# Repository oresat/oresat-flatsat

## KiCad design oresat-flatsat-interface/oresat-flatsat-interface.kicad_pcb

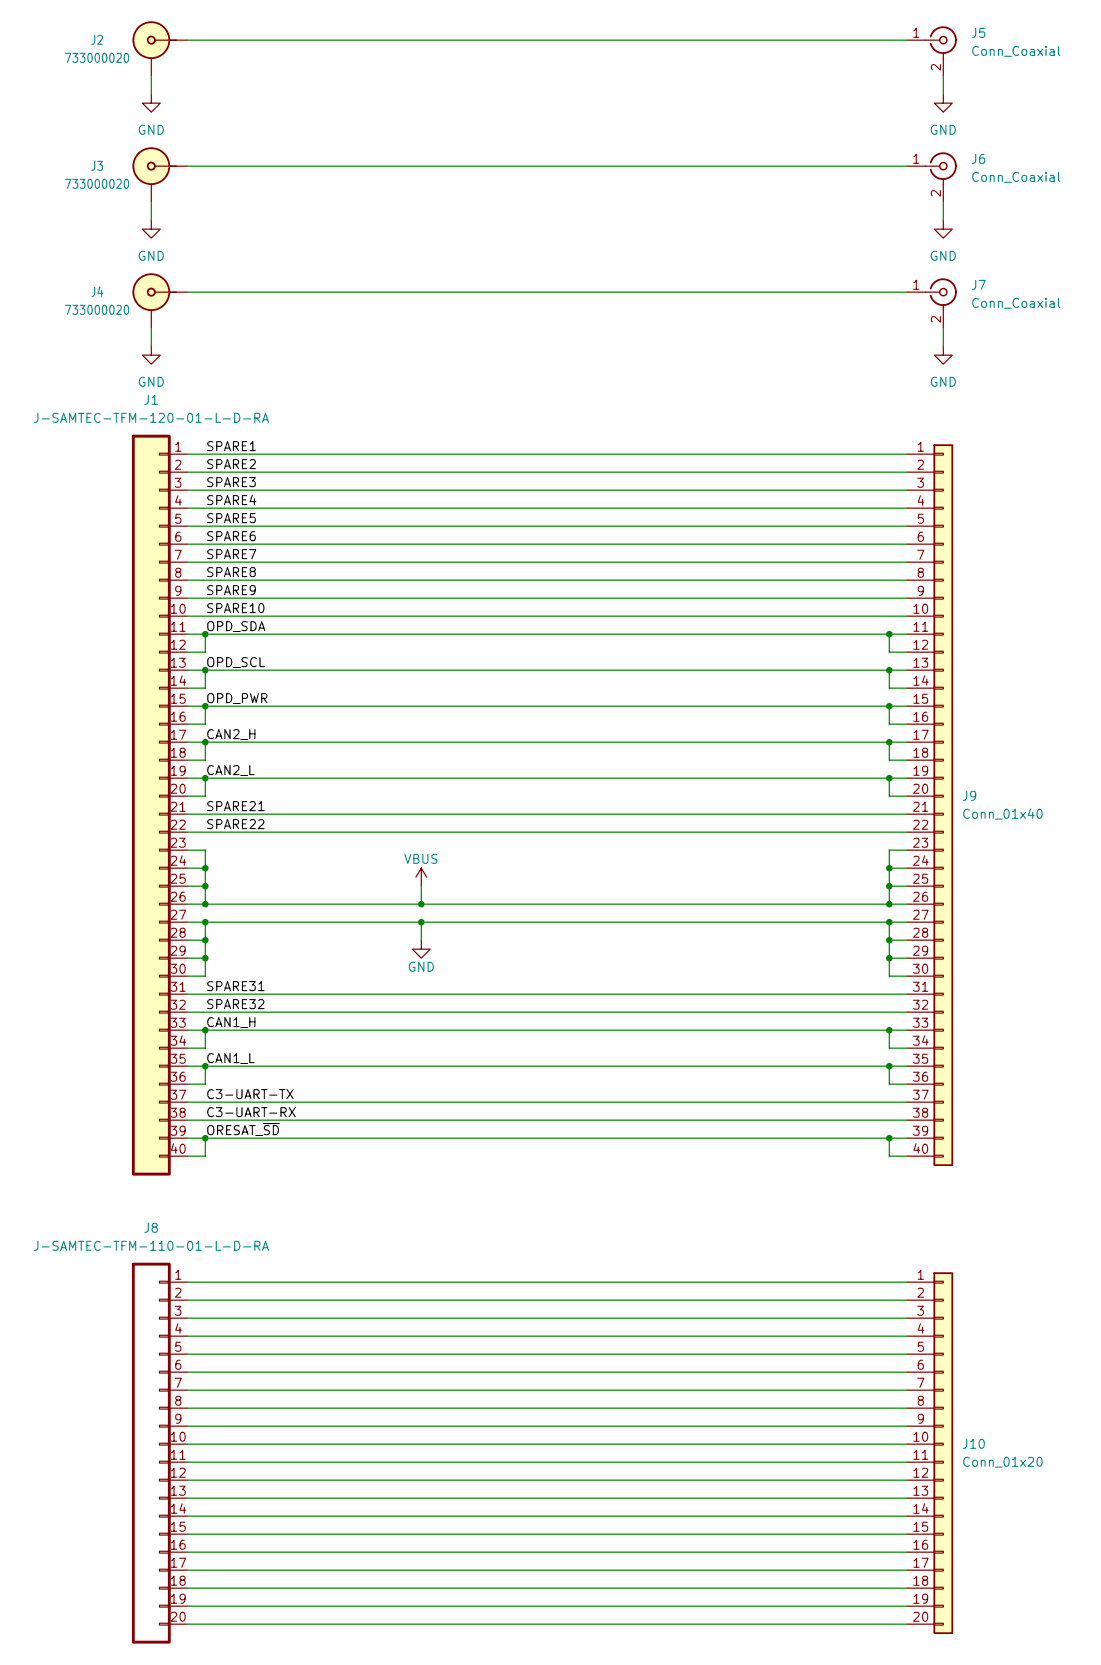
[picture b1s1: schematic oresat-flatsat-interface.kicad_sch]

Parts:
J1: J-SAMTEC-TFM-120-01-L-D-RA; J-SAMTEC-TFM-120-X1-XXX-D-RA-small-pads
J2, J3, J4: 733000020; J-MOLEX-SMPM-073300-002X
J5, J6, J7: Conn_Coaxial; SMA_Amphenol_132289_EdgeMount
J8: J-SAMTEC-TFM-110-01-L-D-RA; J-SAMTEC-TFM-110-X1-XXX-D-RA-small-pads
J9: Conn_01x40; IDC-Header_2x20_P2.54mm_Vertical
J10: Conn_01x20; PinHeader_2x10_P2.54mm_Vertical

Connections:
/C3-UART-RX: J1.38, J9.38
/C3-UART-TX: J1.37, J9.37
/CAN1_H: J1.33, J1.34, J9.33, J9.34
/CAN1_L: J1.35, J1.36, J9.35, J9.36
/CAN2_H: J1.17, J1.18, J9.17, J9.18
/CAN2_L: J1.19, J1.20, J9.19, J9.20
/OPD_PWR: J1.15, J1.16, J9.15, J9.16
/OPD_SCL: J1.13, J1.14, J9.13, J9.14
/OPD_SDA: J1.11, J1.12, J9.11, J9.12
/ORESAT_~SD: J1.39, J1.40, J9.39, J9.40
/SPARE1: J1.1, J9.1
/SPARE2: J1.2, J9.2
/SPARE3: J1.3, J9.3
/SPARE4: J1.4, J9.4
/SPARE5: J1.5, J9.5
/SPARE6: J1.6, J9.6
/SPARE7: J1.7, J9.7
/SPARE8: J1.8, J9.8
/SPARE9: J1.9, J9.9
/SPARE10: J1.10, J9.10
/SPARE21: J1.21, J9.21
/SPARE22: J1.22, J9.22
/SPARE31: J1.31, J9.31
/SPARE32: J1.32, J9.32
GND: J1.27, J1.28, J1.29, J1.30, J2.SHLD, J3.SHLD, J4.SHLD, J5.2 (Ext), J6.2 (Ext), J7.2 (Ext), J9.27, J9.28, J9.29, J9.30
unnamed: J2.SIG, J5.1 (In)
unnamed: J3.SIG, J6.1 (In)
unnamed: J4.SIG, J7.1 (In)
unnamed: J8.1, J10.1
unnamed: J8.2, J10.2
unnamed: J8.3, J10.3
unnamed: J8.4, J10.4
unnamed: J8.5, J10.5
unnamed: J8.6, J10.6
unnamed: J8.7, J10.7
unnamed: J8.8, J10.8
unnamed: J8.9, J10.9
unnamed: J8.10, J10.10
unnamed: J8.11, J10.11
unnamed: J8.12, J10.12
unnamed: J8.13, J10.13
unnamed: J8.14, J10.14
unnamed: J8.15, J10.15
unnamed: J8.16, J10.16
unnamed: J8.17, J10.17
unnamed: J8.18, J10.18
unnamed: J8.19, J10.19
unnamed: J8.20, J10.20
VBUS: J1.23, J1.24, J1.25, J1.26, J9.23, J9.24, J9.25, J9.26

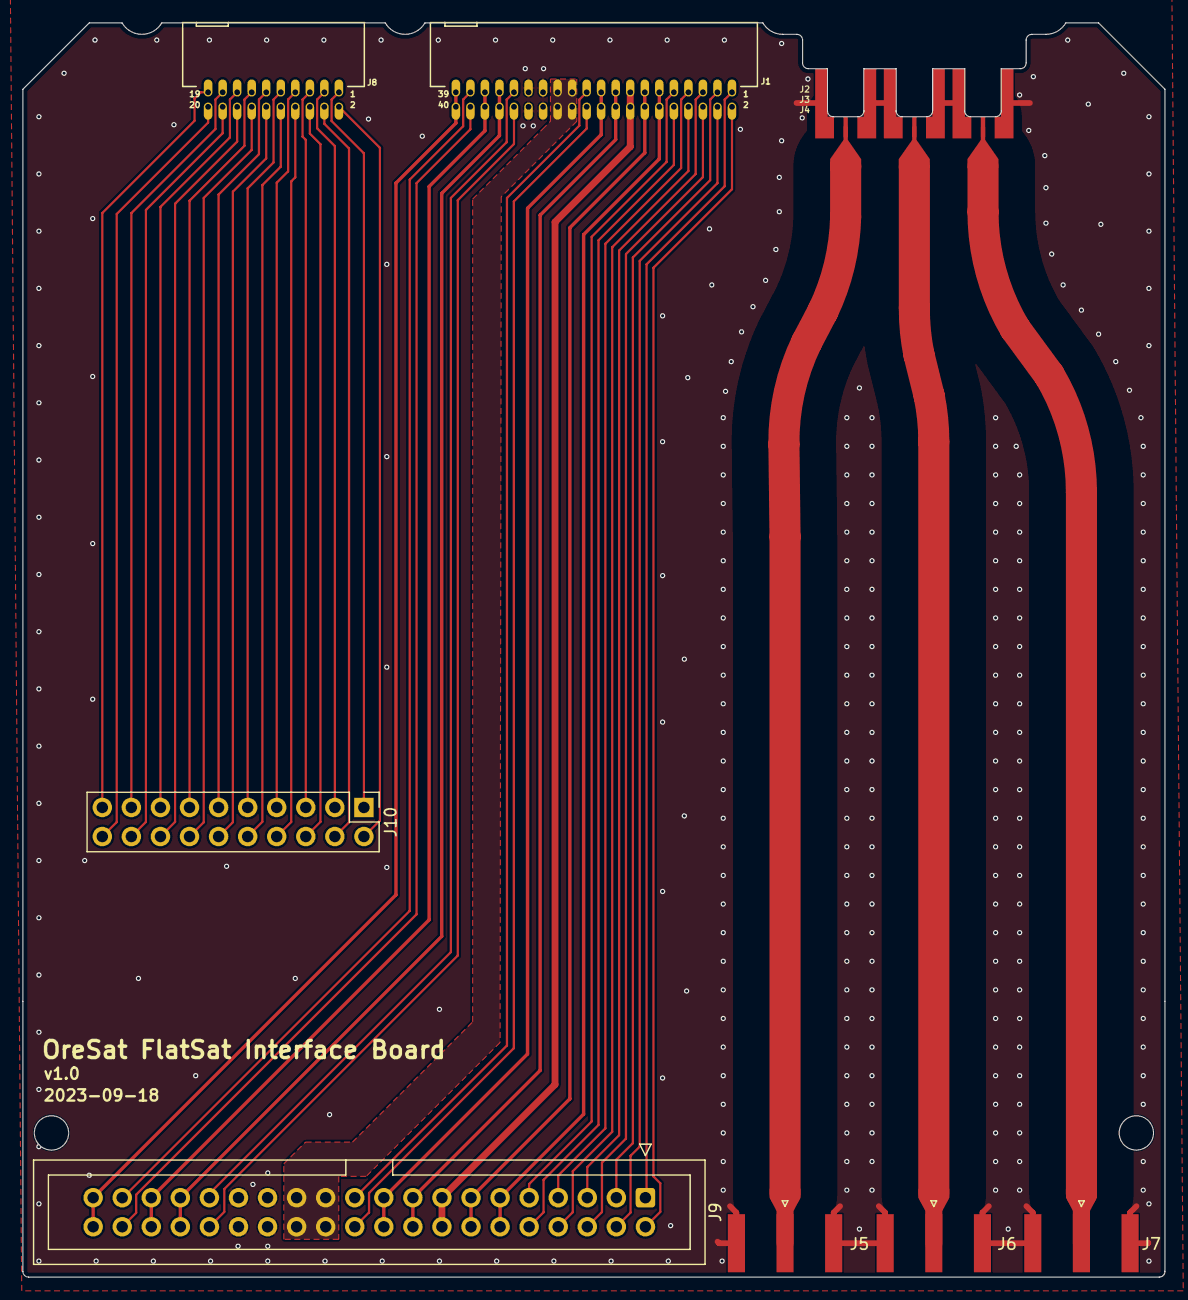
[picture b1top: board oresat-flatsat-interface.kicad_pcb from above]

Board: 2 copper layers, 99.8 x 109.6 mm, 11 parts (0 on the bottom side), 49 nets.

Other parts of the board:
PCB1: ORESAT-CARD-V1.3-FLATSAT

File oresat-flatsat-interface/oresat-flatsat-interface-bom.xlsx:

OreSat OreSat to FlatSat Card Adapter v1.0
Qty | P/NP | Parts | MFR | MPN | Description | Generic | Module | Stock | DIST | DPN | DIST2 | DPN2 | Notes
1 | P | J1 | Samtec | TFM-120-01-L-D-RA | Connector Header Through Hole, Right Angle 40 position 0.050" (1.27mm) | N | Shared | 67 | Digi-Key | SAM10145-ND |  |  | Main card connector
1 | P | J9 | Würth Elektronik | 61204021621 | Connector Header Through Hole 40 position 0.100" (2.54mm) Shrouded | Y | - | 0 | Digi-Key | 732-5401-ND |  |  | 20x2 shrouded 0.1" connector for main IDC cable
1 | P | J8 | Samtec | TFM-110-01-L-D-RA | Connector Header Through Hole, Right Angle 20 position 0.050" (1.27mm) | N | Shared | 18 | Digikey | SAM10113-ND |  |  | Aux card connector
1 | P | J5 | Würth Elektronik | 61202021621 | Connector Header Through Hole 20 position 0.100" (2.54mm) | Y | - | 0 | Digi-Key | 732-2096-ND |  |  | 10x2 shrouded 0.1" connector for aux IDC cable
3 | P | J2, J3, J4 | Molex | 733000020 | Edge mounted SMPM 50ohm Connector | N | Shared | 44 | Digi-Key | WM10772-ND |  |  | RF connectors for backplane (only 1/2 of cards need this)
3 | P | J5, J6, J7 | Amphenol RF | 132289 | SMA Connector Receptacle, Female Socket 50 Ohms Board Edge, End Launch; Panel M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 | Y | - | 0 | Digi-Key | ACX1426-ND |  |  | SMA breakout from backplane (only 1/2 of cards need this)
 |  |  | Date | Notes
 |  |  | 45202 | Created
